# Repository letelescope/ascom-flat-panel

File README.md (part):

# Le Telescope Flat Panel 

[![Build with PlatformIO](https://img.shields.io/badge/build%20with-PlatformIO-orange?logo=data%3Aimage%2Fsvg%2Bxml%3Bbase64%2CPHN2ZyB3aWR0aD0iMjUwMCIgaGVpZ2h0PSIyNTAwIiB2aWV3Qm94PSIwIDAgMjU2IDI1NiIgeG1sbnM9Imh0dHA6Ly93d3cudzMub3JnLzIwMDAvc3ZnIiBwcmVzZXJ2ZUFzcGVjdFJhdGlvPSJ4TWlkWU1pZCI+PHBhdGggZD0iTTEyOCAwQzkzLjgxIDAgNjEuNjY2IDEzLjMxNCAzNy40OSAzNy40OSAxMy4zMTQgNjEuNjY2IDAgOTMuODEgMCAxMjhjMCAzNC4xOSAxMy4zMTQgNjYuMzM0IDM3LjQ5IDkwLjUxQzYxLjY2NiAyNDIuNjg2IDkzLjgxIDI1NiAxMjggMjU2YzM0LjE5IDAgNjYuMzM0LTEzLjMxNCA5MC41MS0zNy40OUMyNDIuNjg2IDE5NC4zMzQgMjU2IDE2Mi4xOSAyNTYgMTI4YzAtMzQuMTktMTMuMzE0LTY2LjMzNC0zNy40OS05MC41MUMxOTQuMzM0IDEzLjMxNCAxNjIuMTkgMCAxMjggMCIgZmlsbD0iI0ZGN0YwMCIvPjxwYXRoIGQ9Ik0yNDkuMzg2IDEyOGMwIDY3LjA0LTU0LjM0NyAxMjEuMzg2LTEyMS4zODYgMTIxLjM4NkM2MC45NiAyNDkuMzg2IDYuNjEzIDE5NS4wNCA2LjYxMyAxMjggNi42MTMgNjAuOTYgNjAuOTYgNi42MTQgMTI4IDYuNjE0YzY3LjA0IDAgMTIxLjM4NiA1NC4zNDYgMTIxLjM4NiAxMjEuMzg2IiBmaWxsPSIjRkZGIi8+PHBhdGggZD0iTTE2MC44NjkgNzQuMDYybDUuMTQ1LTE4LjUzN2M1LjI2NC0uNDcgOS4zOTItNC44ODYgOS4zOTItMTAuMjczIDAtNS43LTQuNjItMTAuMzItMTAuMzItMTAuMzJzLTEwLjMyIDQuNjItMTAuMzIgMTAuMzJjMCAzLjc1NSAyLjAxMyA3LjAzIDUuMDEgOC44MzdsLTUuMDUgMTguMTk1Yy0xNC40MzctMy42Ny0yNi42MjUtMy4zOS0yNi42MjUtMy4zOWwtMi4yNTggMS4wMXYxNDAuODcybDIuMjU4Ljc1M2MxMy42MTQgMCA3My4xNzctNDEuMTMzIDczLjMyMy04NS4yNyAwLTMxLjYyNC0yMS4wMjMtNDUuODI1LTQwLjU1NS01Mi4xOTd6TTE0Ni41MyAxNjQuOGMtMTEuNjE3LTE4LjU1Ny02LjcwNi02MS43NTEgMjMuNjQzLTY3LjkyNSA4LjMyLTEuMzMzIDE4LjUwOSA0LjEzNCAyMS41MSAxNi4yNzkgNy41ODIgMjUuNzY2LTM3LjAxNSA2MS44NDUtNDUuMTUzIDUxLjY0NnptMTguMjE2LTM5Ljc1MmE5LjM5OSA5LjM5OSAwIDAgMC05LjM5OSA5LjM5OSA5LjM5OSA5LjM5OSAwIDAgMCA5LjQgOS4zOTkgOS4zOTkgOS4zOTkgMCAwIDAgOS4zOTgtOS40IDkuMzk5IDkuMzk5IDAgMCAwLTkuMzk5LTkuMzk4em0yLjgxIDguNjcyYTIuMzc0IDIuMzc0IDAgMSAxIDAtNC43NDkgMi4zNzQgMi4zNzQgMCAwIDEgMCA0Ljc0OXoiIGZpbGw9IiNFNTcyMDAiLz48cGF0aCBkPSJNMTAxLjM3MSA3Mi43MDlsLTUuMDIzLTE4LjkwMWMyLjg3NC0xLjgzMiA0Ljc4Ni01LjA0IDQuNzg2LTguNzAxIDAtNS43LTQuNjItMTAuMzItMTAuMzItMTAuMzItNS42OTkgMC0xMC4zMTkgNC42Mi0xMC4zMTkgMTAuMzIgMCA1LjY4MiA0LjU5MiAxMC4yODkgMTAuMjY3IDEwLjMxN0w5NS44IDc0LjM3OGMtMTkuNjA5IDYuNTEtNDAuODg1IDIwLjc0Mi00MC44ODUgNTEuODguNDM2IDQ1LjAxIDU5LjU3MiA4NS4yNjcgNzMuMTg2IDg1LjI2N1Y2OC44OTJzLTEyLjI1Mi0uMDYyLTI2LjcyOSAzLjgxN3ptMTAuMzk1IDkyLjA5Yy04LjEzOCAxMC4yLTUyLjczNS0yNS44OC00NS4xNTQtNTEuNjQ1IDMuMDAyLTEyLjE0NSAxMy4xOS0xNy42MTIgMjEuNTExLTE2LjI4IDMwLjM1IDYuMTc1IDM1LjI2IDQ5LjM2OSAyMy42NDMgNjcuOTI2em0tMTguODItMzkuNDZhOS4zOTkgOS4zOTkgMCAwIDAtOS4zOTkgOS4zOTggOS4zOTkgOS4zOTkgMCAwIDAgOS40IDkuNCA5LjM5OSA5LjM5OSAwIDAgMCA5LjM5OC05LjQgOS4zOTkgOS4zOTkgMCAwIDAtOS4zOTktOS4zOTl6bS0yLjgxIDguNjcxYTIuMzc0IDIuMzc0IDAgMSAxIDAtNC43NDggMi4zNzQgMi4zNzQgMCAwIDEgMCA0Ljc0OHoiIGZpbGw9IiNGRjdGMDAiLz48L3N2Zz4=)](https://platformio.org/)

Open source *ASCOM* and *INDI* driven automated flat panel for astrophotography. 

> ⚠ **DISCLAIMER**  
> This project is still very much work in progress. None of it is likely/expected to work at this stage !

---

## Introduction

This project is an open source initiative, under the MIT license, by *Le Telescope*. This is the v2 of a fully automated and drivable motorized flat panel/dust cap. The device is nicknamed FFFP. Don't ask why! If you still want to know, see the  [misc. section](#miscellaneous) of this readme.

This project should contain all you need to build your own *ASCOM* and/or *INDI* driven Flat Panel. 

- [firmware](./firmware/fffp_firmware/): Firware of the programble chip used to control the panel and its cover
- [drivers](./drivers/): Implementation of the drivers
  - [ASCOM](./drivers/ASCOM/) : Implementation of the *ASCOM* driver 
  - [INDI](./drivers/indi/) : Implementation of the *INDI* driver
- [electronics](./electronics/): Electronic schematics and PCB layouts
- [models](./models/): 3D models for the plat cap
- [specifications](./specifications/): Specifications of the project. Mainly the specs of the communication protocol between the drivers and the firmware.

This project, the protocol, the implementation of both the *ASCOM* driver and the firmware, the electronics and the 3D models are heavily inspired by the the work  of [Dark Sky Geek](https://github.com/jlecomte/). And more precisely: 
- [ascom-flat-panel](https://github.com/jlecomte/ascom-flat-panel)
- [ascom-wireless-flat-panel](https://github.com/jlecomte/ascom-wireless-flat-panel)
- [ascom-telescope-cover-v2](https://github.com/jlecomte/ascom-telescope-cover-v2)

Kudos to him. 

The Pulse Width Modulation (PWM), used to control the panel brightness, implementation is heavily inspired, or more accurately shamelessly ripped, from the work of [Khoih Hoang](https://github.com/khoih-prog) and more precisely [SAMD_PWM](https://github.com/khoih-prog/SAMD_PWM/). 

Kudos to him too.

Finally te INDI driver architecture follows very closely the official [Gemini Flat Panel](https://github.com/indilib/indi/blob/master/drivers/auxiliary/gemini_flatpanel.h) as well as teh [Flip Flat](https://github.com/indilib/indi/blob/master/drivers/auxiliary/flip_flat.h) implemtentations. 

----

## Construction

### Why a "motorized flat panel" ? And what do we mean by "motorized flat panel" ?

In this scenario a flat panel is made of two things
- A light panel with variable brightness
- A motorized cover

The cover is motorized using a servo motor and held in open/close positions using simple magnets. The lightpanel is made 
- either using LEDs and the variable brightness is achieved via pulse width modulation (PWM). 
- or eusing a EL panel and the variable brightness is achived usi a DAC (Digital to Analog Converter) coupled to an OA (Operation Amplifier) in non-inverting amplifier mode. 

This "electronico-mechanical" assembly is controlled via a SAMD21 based board with a custom firmware within a custom PCB. The SAMD21 is particullarly suited because:

- it can output 5V, that is needed to power the servo.
- it can output +3V3 and allow us to choose between 3V and 5V to power the LEDs.
- it has 16 bits timer counters necessary to achieve fast PWM. We do not want flickering flats...
- it has a real DAC output pin to alow "easy" dimming of a flat panel.

One can connect and send commands to the flat-panel using Serial (COM Port) over USB. When plugged in the device will be recognized by windows/linux as a COM device. 

Finally this is driven by ASCOM/INDI, such that one can fully automate taking flats following the acquisition sessions of our beloved night sky targets. 

> ⚠ **DISCLAIMER**  
> This project is built around the Seeeduino XIAO board that uses the ATSAMD21G18A-MU chip. This is the only board that we tested. This may work on other boards that uses these SAMD21 chips, but this may need some rework on the firware, the PCB layout and the mechanical assembly. 

Now that we have the big picture let's get real and build the thing !

[INSERT HERE SOME PHOTOS]

### Pre-requisites

Very few pre-requisites are necessary in order to build the flat panel. More precisely one will need to:

- have access to a 3D printer, to print the mechanical assembly parts
- have some soldering skills and a soldering kit, to solder the components to the custom PCB
- install PlateformIO, to upload the firmware
- love "diy-ing", because you may need to want/need to tweaks things a bit to make it work in your setup. 
  
And that's it ! For instance you won't need software developpement skills as both the driver and the firmware are usable as is. Moreover, the ASCOM driver installer is already pre-compiled and made available to the download. Unfortunaltely one cannot make an "installer" for the arduino firware. Yet using PlaterfomIO to upload the firmware is a matter of three clicks. 

> We chose PlatformIO instead of ArduinoIDE due to recent concerns about Arduino's Open Source commitment under Qualcomm, and ,icing on the cake, PlatformIO provides superior dependency and library management.

### Bill of material 

[TODO] ADD BILL OF MATERIAL 

### Get a coherent version. 

We heavily use the git version control "tags" to label released versions. We also leverage the "GitHub releases" that add the possibility to pin "binaries" (ie anything we want PCB layouts, Driver installers, mechanincal assembly 3D printer files,...) on "tagged" versions. 

When we deem a version is "usable" we tag it, ie we freeze this repository at a particular "commit", and create a release out of it. 

To access the various releases just got the [releases page](https://github.com/letelescope/ascom-flat-panel/releases/) of this repository.

And choose the release you want. The latest should be the "better". 

We recommend that you use one of these released version as they are coherent and tested. Be careful some release are labelled "pre-release" and should be used with caution. Those are developpement, beta and alpha version. Use it at you own risk like all the material on this repository. But even more in this case :D. 

In the same spirit, we do not recommend you use the "head" of the main branch (or any other branch) of this repository as this is work in progress and hence is not guaranteed to be stable or even usable...

> If you already have an FFFPV1, please note that both drivers and firmware **should** be backward compatible. You can use the latest version of both the ASCOM driver with your FFFPV1 without any issue and vice-versa: upload the new firmware on your FFFPV1 device and still use the legacy v1 driver. Yet we recommend you use the latest version of the driver, the firmware, the electronic circuit and the assembly as they all have been improved coherently.

### Electronic circuit

We provide three options for the electronic circuit. The difference is made on wether you want to use a led panel or a EL panel (You may not have the choice, as LED panels are restricted to smaller diameters). 

#### EL Panel option

This is certainely the "go to" solution, as this allows for a slicker and ligther mechanical assembly. Ans the electronics are not that much more difficut. 

- The The Pin "AO" (DAC) of the Seeeduino XIAO is used to control the LED brightness:
  - Is is directly connected to the non-invervint pin of ta TLC272 Op.Amp. The Ration of R1/R2 controls the amplifying contant (R = 1 + R1/R2) 
  - The output of the TLC272 is connected to the base of a  darlington transistor. Such that more current can flow to the EL Driver without worring too much about the life expectency of the TLC272
  -  The +12v needed for the Op Amp and the Driver is obtained using a DC/DC regulator

> ⚠ **WARNING**  
> The choice of Pin AO for DAC is not random. This is the only one on the Seeeduino XIAO (and SAM-D21 chips) capable to produce proper DAC. Please [see](https://ww1.microchip.com/downloads/en/DeviceDoc/SAM_D21_DA1_Family_DataSheet_DS40001882F.pdf). 

- The Pins "5,6,7"  of the Seeeduino XIAO are used for power control, position control and servo feedback:
  - Power control is connected, via a voltage divider bridge, to the gate of a IRLZ34N MOSFET.
  - Feedback is directly connected to the feedback pin of the servo.
  - Position control is directly connected to the position control pin of the servo.
  
- Servo VCC and Servo ground are decoupled using diodes.

- +12V and +5V are decoupled from ground using 10μF capacitors. It acts both as
  - an energy storage for a stable +5V/+12V output.
  - a "wire" for very high frequency spurious oscillations and effectively ground them. 

#### LED Panel schematics

This should be the go solution for most setups. Yet if you setup si particularly slow you may want to check the led versions. 

Here is the schematics for this option

#### LED panel option

There are two options regarding the tension value used to power the LEDs: either +3V3 or +5V. But appart from that the two circuits share the same principles:

- The Pin "8"  of the Seeeduino XIAO is used to control the LED brightness:
  + It is connected, via a voltage divider bridge, to the gate of a IRLZ34N MOSFET.
  - The "+"terminal of the LEDs (strip or panel) is plugged to the constant +3V3 (or +5V) output of the Seeeduino
  - The "-" terminal of the LEDs (strip or panel) is connected to the drain of the IRLZ34N MOSFET. 
  - The source of the MOSFET is grounded. 
  - High frenquency PWM is used to swich rapidly ON and OFF the MOSFET, and allow to control the effective tension applied to the LEDs. 

> ⚠ **WARNING**  
> The choice of Pin 8 for PWM is not random. Not all pins of Seeeduino XIAO (and SAM-D21 chips) are capable to produce high frequency PWM. That's possible with Pin 8 because it use timer counter TCC1 which is 16bits.  And If you want to choose another pin please check the [documentation](https://ww1.microchip.com/downloads/en/DeviceDoc/SAM_D21_DA1_Family_DataSheet_DS40001882F.pdf) first. 

- The Pins "5,6,7"  of the Seeeduino XIAO are used for power control, position control and servo feedback:
  - Power control is connected, via a voltage divider bridge, to the gate of a IRLZ34N MOSFET.
  - Feedback is directly connected to the feedback pin of the servo.
  - Position control is directly connected to the position control pin of the servo.
  
- Servo VCC and Servo ground are decoupled using diodes.

- +5V (and +3V3 if needed) are decoupled from ground using 10μF capacitors. It acts both as
  - an energy storage for a stable +5V/+3V3 output.
  - a "wire" for very high frequency spurious oscillations and effectively ground them. 

##### The +3V3 output for LEDs

This is best suited for small refractors using fewer LEDs and/or fast optics. 

Here is the schematics for this option

##### The +5V output for LEDs

This is best suited for bigger tubes using a larger number of LEDs drawing more current. 

#### Cicruit layout breadbord validation

We recommend you prototype the circuit using breadbords first. 

- This can help you choose between the +5V and +3V3 version. A quick "hint", don't go for to bright ouputs for LEDs as a very bright panel is in fact not really needed when taking flats. Especially with fast optics. 
- This allows to check each component/part of the circuit independently. It's always better to find a faulty component before it is soldered on a PCB.
- It's always fun to prototype. 

Here is and example of what the "+5V" circuit may look like on a breadbord.

.

#### Printed Circuit Board

We had our PCBs printed by [PCBWay](https://www.pcbway.com/). If you do not modify the PCB layout and want to have it printed by PCBWay, you can just download one of the provided zip files that are pinned to the release (fffpv1-electronics-5V-LEDs-pcbway-files.zip or fffpv1-electronics-3V-LEDs-pcbway-files.zip, depending if you intend to use the +5V or +3V3 version).

If you want to modify the PCB layout, you have two options depending on the company you chose to print your PCB :
- If you chose PCBWay, just run a "Desing Rules Check" after your modifications are done to make sure there is no error (there may be warnings, but who cares about warnings ?). The PCBWay design rules are associated to the KiCAD project (they are implemented in the ascom-flat-panel.kicad_dru file). From here you can generate the fabrication files using the KiCAD interface and following the recommandations explained on the PCBWay website, OR you can simply install the PCBWay plugin for KiCAD, which will do the job for you in one click, and will drive you to the PCBWay website to complete your order (yes, we live in a fantastic era).
- If you chose another company, make sure their design rules are implemented to the KiCAD project. Depending on the company, you may find them in tables on the company's website and implement them using the KiCAD interface, or they can provide a .kicad_dru file you can use instead of the one we provide. Then perform a "Desing Rules Check" to check your modifications. Then you can generate the fabrication files using the KiCAD interface and following the recommandations provided by your supplier, or you can find out if there is a KiCAD plugin to do the job. Some suppliers will just take your KiCAD project and do all of this by their own, leaving you with basically nothing to do but creating an account and uploading your project (and pay, of course).

#### Firmware upload

#### Pre-requisite

The firmware needs to be uploaded using Visual Studio Code/PlateformIO . [PlateformIO setup section](#pre-requisites-1) of this documentation to set it. 

#### Upload the firware

1. Open the [firmware project](./firmware/fffp) from Visula Strudio Code/Plateform-IO. 

2. Connect the board via US. 
   
3. Select the board.
   
4. Click the "arrow" at the bottom to compile and upload the firmware on the board. 

The output should look something like: 

#### Firmware checks

Once the firware is uploaded, do not disconnect the board yet. Still from the Arduino IDE open the "Serial Monitor". Once connected, in the console type:

``` console
COMMAND:PING
```
the board should answer

``` console
RESULT:PONG
```

Congrats! The Seeeduino is ready to act as your flat panel controller !

### Mechanical Assembly

Moving on to the actual print and build of the assembly. 

#### Prints from pre-designed assemblies

This repository (and therefore the tagged release version) contains a fully fonctional model. This is made to fit an Askar SQA-55 and uses premade 100mm led panel. It also feature an adapter to fit an Askar 71F. 

"Ready to print" STL files are also pinned to the release. Just download the fffpv1-100mm_led_pan_diam_stl.zip archive, unzip it. The archiver files are organized within two folders "Black" and "White". Files in he "black" repository can be printed in the color of your choice, but the one in the "white" folder should be printed using white PLA for better performance. This is especially true for the "spacer/diffuser" that, as its name suggests, helps homogenise the illumination of the panel.

#### Modification of pre-designed assemblies

#### Manufacturing sequence

#### Calibration of servo motor 

> ⚠ **WARNING**
> The firmware needs to be calibrated.

At first boot the LEDs will flash to indicate that it needs to be calibrated. 

> ⚠ **WARNING**
> Disconnect the servo from the mecanical assembly before launching the calibration procedure. 

Then from the IDE connect to the board and using the Arduino serial monitor send (type) the "command" 

``` console
COMMAND:COVER_CALIBRATION_RUN
``` 

The device should perform its calibration procedure and reply with 

``` console
RESULT:COVER_CALIBRATION_RUN@OK
```

Once it has completed, re-attach the right arm to the servo. The device is now ready to be used.

### ASCOM Driver Install

You can either used the installer to install the ASCOM driver or build it from source. For the sake of simplicity we recommend using the installer. 

#### Pre-compiled installer

The installer is pined on each release [releases page](https://github.com/letelescope/ascom-flat-panel/releases/). 

1. From the wanted release, download the file "FFFP_Setup.exe". 

2. "Double-click" on the downloaded file to launch it. 

   > ⚠ **WARNING**
   > Windows will warn that the publisher is unknown. This is perfectly fine. As buying a verified signing key, is definitely not a priority for us, we could not sign the installer. Yet this is perfectly safe to use it. 

3. Follow the instruction to install and register the driver. 

Congrats! You just installed the driver !

#### Build from sources

To build it from source please check the relevant section of the "developpement documentation". 

#### Driver validation

Once install is complete, one can use the ASCOM profile explorer tool to check that this was installed properly. From the ASCOM profile explorer check that the *ASCOM CoverCalibrator Drvier for Le Telescope FFFP* is listed in the Cover Calibrators. 

### INDI Driver

> ⚠ **WARNING**
> INDO driver is NOT functional DO NOT USE IT. 

---

## Testing

To avoid mass troubleshooting, one can test each component fairly separately. Below are listed some tests that can be used to validate the setup. Going from "unit test" to big-bang integration tests from your favourite acquisition software. 

### Firware "unit" testing

Once the firware is uploaded, one should already have tested that the seeduino was responsive. If not, reconnect the board via USB. From the Arduino IDE, open the "Serial Monitor". Once connected, in the console type:

``` console
COMMAND:PING
```
the board should answer

``` console
RESULT:PONG
```
If that's not the case, please make sure that you uploaded the (correct version of the) firmware firt. 

If that is indeed the case, congrats you are ready to test more "interesting" features of the firmware.

#### Set brightness levels

From the "Serial Monitor", in the console type the following command to adjust the LED panel brightness level:

``` console
COMMAND:BRIGHTNESS_SET@1024
```
the board should answer in the console

``` console
RESULT:BRIGHTNESS_SET@1024
```
In parallel, if it is connected to the board, the light panel should have been turned on. Feel free to change the value (number after the '@') to adjust the brightness. Max allowed value is 2047 and min value is 0. 

Use ```COMMAND:BRIGHTNESS_RESET``` to switch off the panel.

Congrats the variable light panel is functionnal. 

#### Open/Close the cover

> ⚠ **WARNING**
> To be able to open/close the panel, the panel should be calibrated first. Check the "mechanical assembly" section for the procedure. 

When turned on, the panel should be closed. To open it, from the "Serial Monitor", in the console type the following command:

``` console
COMMAND:COVER_OPEN
```
the panel should start moving and the board should answer in the console

``` console
RESULT:COVER_OPEN@OK
```

Once open to close it simply type in the consle

``` console
COMMAND:COVER_CLOSE
```
the panel should start moving and the board should answer in the console

``` console
RESULT:COVER_CLOSE@OK
```

Finally at any given time, to know the status of the mecanical panel type 

``` console
COMMAND:COVER_GET_STATE
```
the panel should start moving and the board should answer in the console

``` console
RESULT:COVER_GET@{panel.cover}
```

where panel.cover is string human readable translation of the current cover state. Possible values are in [**OPEN**, **OPENING**, **CLOSING**,]; 

Congrats the motorized cover is functionnal. 

### Driver "unit testing"

After install completion, one should already have used the ASCOM profile explorer tool to check that this was installed properly. If that's not the case from the ASCOM profile explorer check that the *ASCOM CoverCalibrator Drvier for Le Telescope FFFP* is listed in the Cover Calibrators. 

1. Then check that the driver is instiable using the ASCOM diagnostic tools
   
   a. Select the "Cover Calibrator" device type and elect the "FFPV1 Cover Calibrator"

   b. Find and configure the "properties" of the driver

   b. Connect to the driver. Expect nothing much to happen. 

Congrats the driver seems to work as expected !

### Connect to the panel from N.I.N.A via ASCOM

Great ! If you read this, at this stage, the firware, the driver and the mecanical assembly should work, or at least one should be confident enough that they are working. Let's make the final test (and the only one relevant in fact). Let's take some flats from N.I.N.A. 

## Usage

The FFFP should be now be fully usable and drivable from N.I.N.A. 

### Flat-Panel Connection

Let's connect to the flat panel. 

0. Plug the flat panel to the computer via USB

In the equipment tab, from the flat panel section:

1. Select the *ASCOM CoverCalibrator Drvier for Le Telescope FFFP*.
2. Click the gear icon and select the correct COM Port. 
3. Hit OK to save the configuration.

4. Click the "power" button to connect to the flat panel. 

From there you can turn on and off the panel, set the wanted brightness and/or open/close the cover. 

### N.I.N.A smart flats

Let's now use the N.I.N.A smart flats capabilities to automate flat frames recording.

#### Auto-exposure

#### Auto-brightness

---

## Developpement 

### Principle

In this scenario a flat panel is made of two things
- A light panel with variable brightness
- A motorized cover

The firmware updates the state of the flat panel upon instructions of the (*ASCOM* or *INDI*) driver. The communication protocol is serial based. The serial connection is established via USB. Here is a a summary of the protocol 
- Both the driver and the flat panel (its firmware) exchange single line messages; ie terminated by '\n'.
- A message is structured as TYPE:MESSAGE, where TYPE is in "COMMAND, RESULT, ERROR" and MESSAGE is alaphanumerical with spaces and "@"

The driver emmits and the firmware handles the incoming "COMMAND" messages. This kind of message is stuctured as 

- `COMMAND:NAME[@ARGS]` where NAME is [A-Z_]+ and ARGS may be optional or mandatory and their nature may depend on the command.

The firmware then responds with 
- either a `RESULT:CMD_NAME@VALUE` if operation succeeded
- or an `ERROR:ERR_MESSAGE@DETAILS` if anything went wrong

In a nutshell

     -----------------                           ------------
    |                 |                         |            |
    |      Driver     | COMMAND:CMD_NAME[@ARGS] | Flat Panel |
    | (ASCOM or INDI) | --------------------->  | (firmware) |
    |                 | <---------------------  |            |
     -----------------  RESULT:CMD_NAME@VALUE    ------------
                                or
                        ERROR:ERR_MESSAGE@DETAILS

More details on this protocol are provided in [protocol.md](./specifications/protocol.md)

### Softwares developpement and compilations

#### Seeduino firmware

The firware is entirely buildable and uploadable using the Arduino IDE
 
##### Pre-requisites 

- [Download](https://code.visualstudio.com/download) and install the Visual Studio Code or the IDE of your choice
- [Download](https://platformio.org/install/ide) PlatformIO IDE and/or install the PlatformIO extension for Visual Studio Code
- No need to download and configure the Seeduino XIAO board for PlateformIO as this is already done in the [platformio.ini](./firmware/fffp_firmware/platformio.ini) file of the firmware project.
- No need to download and install the official Adafruit SleepyDog library  as this is already done in the [platformio.ini](./firmware/fffp_firmware/platformio.ini). This is used to properly handle disconnection. 

##### Compile and upload the firmware

1) Using PlateformIO IDE, open the [project](./firmware/fffp_firmware/)

2) Click "PlateformIO: Build" to compile the firmware. The output should be something like 
   ``` console
   Processing seeed_xiao (platform: atmelsam; board: seeed_xiao; framework: arduino)
   --------------------------------------------------------------------------------------------------------------------------------------------------
   Verbose mode can be enabled via `-v, --verbose` option
   CONFIGURATION: https://docs.platformio.org/page/boards/atmelsam/seeed_xiao.html
   PLATFORM: Atmel SAM (8.3.0) > Seeeduino XIAO
   HARDWARE: SAMD21G18A 48MHz, 32KB RAM, 256KB Flash
   DEBUG: Current (atmel-ice) External (atmel-ice, blackmagic, jlink)
   PACKAGES:
    - framework-arduino-samd-seeed @ 1.8.5
    - framework-cmsis @ 2.50400.181126 (5.4.0)
    - framework-cmsis-atmel @ 1.2.2
    - toolchain-gccarmnoneeabi @ 1.70201.0 (7.2.1)
   LDF: Library Dependency Finder -> https://bit.ly/configure-pio-ldf
   LDF Modes: Finder ~ chain, Compatibility ~ soft
   Found 20 compatible libraries
   Scanning dependencies...
   Dependency Graph
   |-- Servo @ 1.3.0
   |-- Adafruit SleepyDog Library @ 1.6.5
   |-- FF_Flat_Panel
   |-- FlashStorage @ 0.5.0
   |-- SAMD21_PWM
   Building in release mode
   Compiling .pio\build\seeed_xiao\src\main.cpp.o
   Compiling .pio\build\seeed_xiao\libae5\Servo\avr\Servo.cpp.o
   Compiling .pio\build\seeed_xiao\libae5\Servo\esp32\Servo.cpp.o
   Compiling .pio\build\seeed_xiao\libae5\Servo\mbed\Servo.cpp.o
   Compiling .pio\build\seeed_xiao\libae5\Servo\megaavr\Servo.cpp.o
   Compiling .pio\build\seeed_xiao\libae5\Servo\nrf52\Servo.cpp.o
   Compiling .pio\build\seeed_xiao\libae5\Servo\renesas\Servo.cpp.o
   Compiling .pio\build\seeed_xiao\libae5\Servo\sam\Servo.cpp.o
   Compiling .pio\build\seeed_xiao\libae5\Servo\samd\Servo.cpp.o
   Compiling .pio\build\seeed_xiao\libae5\Servo\stm32f4\Servo.cpp.o
   Compiling .pio\build\seeed_xiao\libae5\Servo\xmc\Servo.cpp.o
   Compiling .pio\build\seeed_xiao\libae5\Servo\zephyr\Servo.cpp.o
   Compiling .pio\build\seeed_xiao\lib2bf\Adafruit SleepyDog Library\Adafruit_SleepyDog.cpp.o
   Compiling .pio\build\seeed_xiao\lib2bf\Adafruit SleepyDog Library\utility\WatchdogAVR.cpp.o
   Compiling .pio\build\seeed_xiao\lib2bf\Adafruit SleepyDog Library\utility\WatchdogESP32.cpp.o
   Compiling .pio\build\seeed_xiao\lib2bf\Adafruit SleepyDog Library\utility\WatchdogESP8266.cpp.o
   Compiling .pio\build\seeed_xiao\lib2bf\Adafruit SleepyDog Library\utility\WatchdogKinetisK.cpp.o
   Compiling .pio\build\seeed_xiao\lib2bf\Adafruit SleepyDog Library\utility\WatchdogKinetisL.cpp.o
   Compiling .pio\build\seeed_xiao\lib2bf\Adafruit SleepyDog Library\utility\WatchdogNRF.cpp.o
   Compiling .pio\build\seeed_xiao\lib2bf\Adafruit SleepyDog Library\utility\WatchdogRP2040.cpp.o
   Compiling .pio\build\seeed_xiao\lib2bf\Adafruit SleepyDog Library\utility\WatchdogSAMD.cpp.o
   Compiling .pio\build\seeed_xiao\libc78\FlashStorage\FlashStorage.cpp.o
   Archiving .pio\build\seeed_xiao\libae5\libServo.a
   Compiling .pio\build\seeed_xiao\FrameworkArduinoVariant\variant.cpp.o
   Compiling .pio\build\seeed_xiao\FrameworkArduino\IPAddress.cpp.o
   Compiling .pio\build\seeed_xiao\FrameworkArduino\IPv6Address.cpp.o
   Archiving .pio\build\seeed_xiao\lib2bf\libAdafruit SleepyDog Library.a
   Compiling .pio\build\seeed_xiao\FrameworkArduino\Print.cpp.o
   Compiling .pio\build\seeed_xiao\FrameworkArduino\Reset.cpp.o
   Compiling .pio\build\seeed_xiao\FrameworkArduino\Retarget.cpp.o
   Compiling .pio\build\seeed_xiao\FrameworkArduino\SERCOM.cpp.o
   Archiving .pio\build\seeed_xiao\libc78\libFlashStorage.a
   Archiving .pio\build\seeed_xiao\libFrameworkArduinoVariant.a
   Compiling .pio\build\seeed_xiao\FrameworkArduino\Stream.cpp.o
   Compiling .pio\build\seeed_xiao\FrameworkArduino\StreamString.cpp.o
   Compiling .pio\build\seeed_xiao\FrameworkArduino\Tone.cpp.o
   Compiling .pio\build\seeed_xiao\FrameworkArduino\USB\CDC.cpp.o
   Compiling .pio\build\seeed_xiao\FrameworkArduino\USB\PluggableUSB.cpp.o
   Compiling .pio\build\seeed_xiao\FrameworkArduino\USB\SAMD21_USBDevice.cpp.o
   Compiling .pio\build\seeed_xiao\FrameworkArduino\USB\USBCore.cpp.o
   Compiling .pio\build\seeed_xiao\FrameworkArduino\USB\samd21_host.c.o
   Compiling .pio\build\seeed_xiao\FrameworkArduino\Uart.cpp.o
   Compiling .pio\build\seeed_xiao\FrameworkArduino\WInterrupts.c.o
   Compiling .pio\build\seeed_xiao\FrameworkArduino\WMath.cpp.o
   Compiling .pio\build\seeed_xiao\FrameworkArduino\WString.cpp.o
   Compiling .pio\build\seeed_xiao\FrameworkArduino\abi.cpp.o
   Compiling .pio\build\seeed_xiao\FrameworkArduino\avr\dtostrf.c.o
   Compiling .pio\build\seeed_xiao\FrameworkArduino\base64.cpp.o
   Compiling .pio\build\seeed_xiao\FrameworkArduino\cbuf.cpp.o
   Compiling .pio\build\seeed_xiao\FrameworkArduino\cortex_handlers.c.o
   Compiling .pio\build\seeed_xiao\FrameworkArduino\delay.c.o
   Compiling .pio\build\seeed_xiao\FrameworkArduino\hooks.c.o
   Compiling .pio\build\seeed_xiao\FrameworkArduino\itoa.c.o
   Compiling .pio\build\seeed_xiao\FrameworkArduino\libb64\cdecode.c.o
   Compiling .pio\build\seeed_xiao\FrameworkArduino\libb64\cencode.c.o
   Compiling .pio\build\seeed_xiao\FrameworkArduino\main.cpp.o
   Compiling .pio\build\seeed_xiao\FrameworkArduino\math_helper.c.o
   Compiling .pio\build\seeed_xiao\FrameworkArduino\new.cpp.o
   Compiling .pio\build\seeed_xiao\FrameworkArduino\pulse.c.o
   Compiling .pio\build\seeed_xiao\FrameworkArduino\pulse_asm.S.o
   Compiling .pio\build\seeed_xiao\FrameworkArduino\startup.c.o
   Compiling .pio\build\seeed_xiao\FrameworkArduino\wiring.c.o
   Compiling .pio\build\seeed_xiao\FrameworkArduino\wiring_analog.c.o
   Compiling .pio\build\seeed_xiao\FrameworkArduino\wiring_digital.c.o
   Compiling .pio\build\seeed_xiao\FrameworkArduino\wiring_private.c.o
   Compiling .pio\build\seeed_xiao\FrameworkArduino\wiring_pwm.cpp.o
   Compiling .pio\build\seeed_xiao\FrameworkArduino\wiring_shift.c.o
   C:\Users\fgautier\.platformio\packages\framework-arduino-samd-seeed\cores\arduino\wiring_analog.c:35:12: warning: '_dacResolution' defined but not used [-Wunused-variable]
    static int _dacResolution = 10;
               ^~~~~~~~~~~~~~
   C:\Users\fgautier\.platformio\packages\framework-arduino-samd-seeed\cores\arduino\wiring_pwm.cpp: In function 'void noPwm(uint32_t)':
   C:\Users\fgautier\.platformio\packages\framework-arduino-samd-seeed\cores\arduino\wiring_pwm.cpp:374:13: warning: unused variable 'tcChannel' [-Wunused-variable]
        uint8_t tcChannel = GetTCChannelNumber(pinDesc.ulPWMChannel);
                ^~~~~~~~~
   Archiving .pio\build\seeed_xiao\libFrameworkArduino.a
   Linking .pio\build\seeed_xiao\firmware.elf
   c:/users/fgautier/.platformio/packages/toolchain-gccarmnoneeabi/bin/../lib/gcc/arm-none-eabi/7.2.1/../../../../arm-none-eabi/bin/ld.exe: warning: changing start of section .bss by 4 bytes
   c:/users/fgautier/.platformio/packages/toolchain-gccarmnoneeabi/bin/../lib/gcc/arm-none-eabi/7.2.1/../../../../arm-none-eabi/bin/ld.exe: warning: changing start of section .bss by 4 bytes
   c:/users/fgautier/.platformio/packages/toolchain-gccarmnoneeabi/bin/../lib/gcc/arm-none-eabi/7.2.1/../../../../arm-none-eabi/bin/ld.exe: warning: changing start of section .bss by 4 bytes
   c:/users/fgautier/.platformio/packages/toolchain-gccarmnoneeabi/bin/../lib/gcc/arm-none-eabi/7.2.1/../../../../arm-none-eabi/bin/ld.exe: warning: changing start of section .bss by 4 bytes
   c:/users/fgautier/.platformio/packages/toolchain-gccarmnoneeabi/bin/../lib/gcc/arm-none-eabi/7.2.1/../../../../arm-none-eabi/bin/ld.exe: warning: changing start of section .bss by 4 bytes
   Checking size .pio\build\seeed_xiao\firmware.elf
   Advanced Memory Usage is available via "PlatformIO Home > Project Inspect"
   RAM:   [=         ]   9.4% (used 3064 bytes from 32768 bytes)
   Flash: [==        ]  15.2% (used 39768 bytes from 262144 bytes)
   Building .pio\build\seeed_xiao\firmware.bin
   ========================================================== [SUCCESS] Took 7.97 seconds ==========================================================
   ```

   Don't worry to much about the warnings. Those are only warnings and can be safely igonered c.f. [arduino forum](https://forum.arduino.cc/t/web-ide-error-changing-start-of-section-by-4-bytes/1218049) and [adafruit forum](https://forums.adafruit.com/viewtopic.php?t=189483#p917530) .

1) Connect the Seeeduino and  "PlateformIO: Build"to test it

##### Warning - Firmware calibrarion

The firmware needs to be calibrated. At first boot the leds will flash to indicate that it needs to be calibrated. 

> **WARNING**
> Disconnect the servo from the mecanical assembly before launching the calibration procedure. 

Then from the IDE connect to the board and using the Arduino serial monitor send (type) the "command" 

``` console
COMMAND:COVER_CALIBRATION_RUN
``` 

The device should perform its calibration procedure and reply with 

``` console
RESULT:COVER_CALIBRATION_RUN@OK
```

Once it has completed, re-attach the right arm to the servo. The device is now ready to be used.

#### ASCOM Driver

The ASCOM driver is a C# .Net project that have been first created using the ASCOM 6 Visual Studio 2022 templates. Hence we recommend using Visual Studio 2022 when building it. Feel free to change this procedure to match your tooling. 

##### Pre-requisites 
 
- [ASCOM 7](https://github.com/ASCOMInitiative/ASCOMPlatform/releases/tag/v7.1.1) plateform
- [Visual Studio 2022](https://visualstudio.microsoft.com/fr/vs/). Comunity edition is totally fine. 
- A fully functional [ASCOM developper environement](https://ascom-standards.org/COMDeveloper/Index.htm) . Especiall, you may want to add the ASCOM "extensions" to Visual Studio.

##### Compile and register the driver

1) Open the ["solution"](./drivers/ASCOM/ASCOM_7_Driver/ASCOM_7_Driver.sln) from Visual Studio 2022

2) Compile the project using "Ctrl + Shift + B". The result in the console should look something like
  
   ``` console
   Génération démarrée à 14:12...
   1>------ Début de la génération : Projet : ASCOM_7_Driver, Configuration : Debug Any CPU ------
   1>  ASCOM_6_Driver -> D:\Documents\Perso\Astro\diy\ascom-flat-panel\ASCOM_drivers\ASCOM_7_Driver\bin\Debug\ASCOM.LeTelescopeFFFPV1.exe
   ========== Build : 1 réussite(s), 0 échec(s), 0 à jour, 0 ignorée(s) ==========
   ========== Build s’est terminée à 14:12 et a duré 10,405 secondes ==========
   ```

3) The first time you compile the server you must "register it" on the ASCOM plateform. Open an "elevated" command prompt (with admin priviledges) at the folder where the local server executable is located. Run the local server exe with the /regserver parameter which will create the entry that appears in the ASCOM Chooser. 
  
   ``` console
   .\ASCOM.LeTelescopeFFFP.exe /regserver
   ```

   **This registration only needs to be done once*.

4) You can now launch the driver from any ASCOM client, e.g. N.I.N.A or the ASCOM Diagnostic tool

##### Warning - When used with N.I.N.A

As of N.I.N.A 3.1.HF2, the "ASCOM device instance reference " is not disposed when connection failed. In our setup this may happen if the flat panel is not connected to the PC. In this scenario, the connection will fail, but a "driver process" will hang, waiting for N.I.N.A to dispose of the reference.

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
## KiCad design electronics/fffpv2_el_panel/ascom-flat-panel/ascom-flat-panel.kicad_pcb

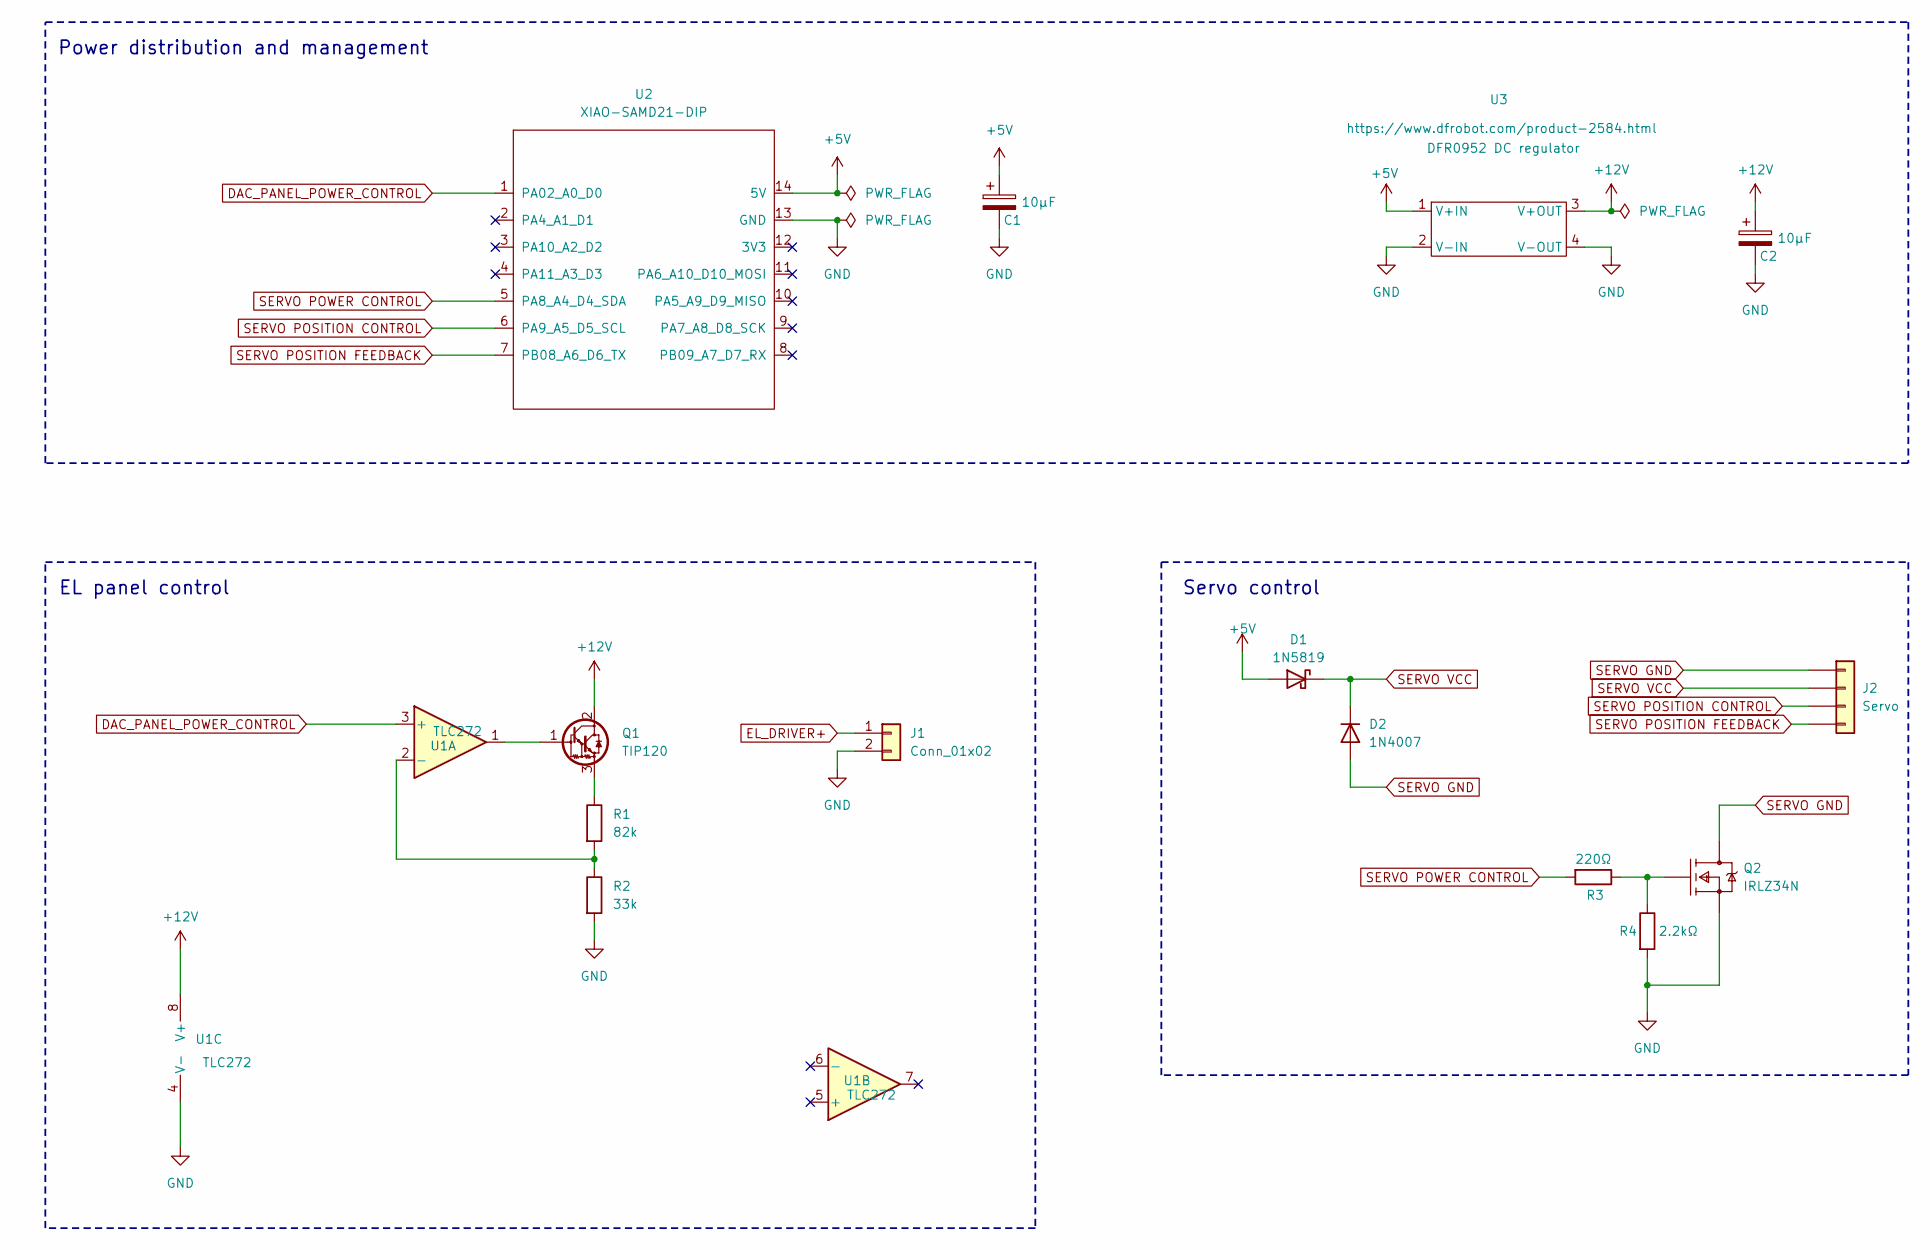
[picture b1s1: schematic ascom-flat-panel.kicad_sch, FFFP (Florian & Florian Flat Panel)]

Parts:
C1, C2: 10µF; C_Radial_D6.3mm_H11.0mm_P2.50mm
D1: 1N5819; D_DO-41_SOD81_P10.16mm_Horizontal
D2: 1N4007; D_DO-41_SOD81_P10.16mm_Horizontal
J1: Conn_01x02; JST_XH_B2B-XH-A_1x02_P2.50mm_Vertical
J2: Servo; PinHeader_1x04_P2.54mm_Vertical
Q1: TIP120; TO-220-3_Vertical
Q2: IRLZ34N; TO-220-3_Vertical; breakdown voltage drain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 60 V; current rating 32 A; mouser part number 512-FQP30N06L; digikey description MOSFET N-CH 60V 32A TO-220
R1: 82k; R_Axial_DIN0207_L6.3mm_D2.5mm_P10.16mm_Horizontal
R2: 33k; R_Axial_DIN0207_L6.3mm_D2.5mm_P10.16mm_Horizontal
R3: 220Ω; R_Axial_DIN0207_L6.3mm_D2.5mm_P10.16mm_Horizontal
R4: 2.2kΩ; R_Axial_DIN0207_L6.3mm_D2.5mm_P10.16mm_Horizontal
U1: TLC272; DIP-8_W7.62mm
U2: XIAO-SAMD21-DIP
U3: DFR052 DC regulator

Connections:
+5V: C1.1, D1.2 (A), U2.14 (5V), U3.1 (V+IN)
+12V: C2.1, Q1.2 (C), U1.8 (V+), U3.3 (V+OUT)
DAC_PANEL_POWER_CONTROL: U1.3 (+), U2.1 (PA02_A0_D0)
EL_DRIVER+: Q1.3 (E), R1.1; also elsewhere on the board
GND: C1.2, C2.2, J1.2, Q2.3 (S), R2.2, R4.2, U1.4 (V-), U2.13 (GND), U3.2 (V-IN), U3.4 (V-OUT); also elsewhere on the board
unnamed: Q1.1 (B), U1.1
unnamed: Q2.1 (G), R3.1, R4.1
unnamed: R1.2, R2.1, U1.2 (-)
SERVO GND: D2.2 (A), J2.1, Q2.2 (D)
SERVO POSITION CONTROL: J2.3, U2.6 (PA9_A5_D5_SCL)
SERVO POSITION FEEDBACK: J2.4, U2.7 (PB08_A6_D6_TX)
SERVO POWER CONTROL: R3.2, U2.5 (PA8_A4_D4_SDA)
SERVO VCC: D1.1 (K), D2.1 (K), J2.2

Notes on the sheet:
Servo control
Power distribution and management
EL panel control

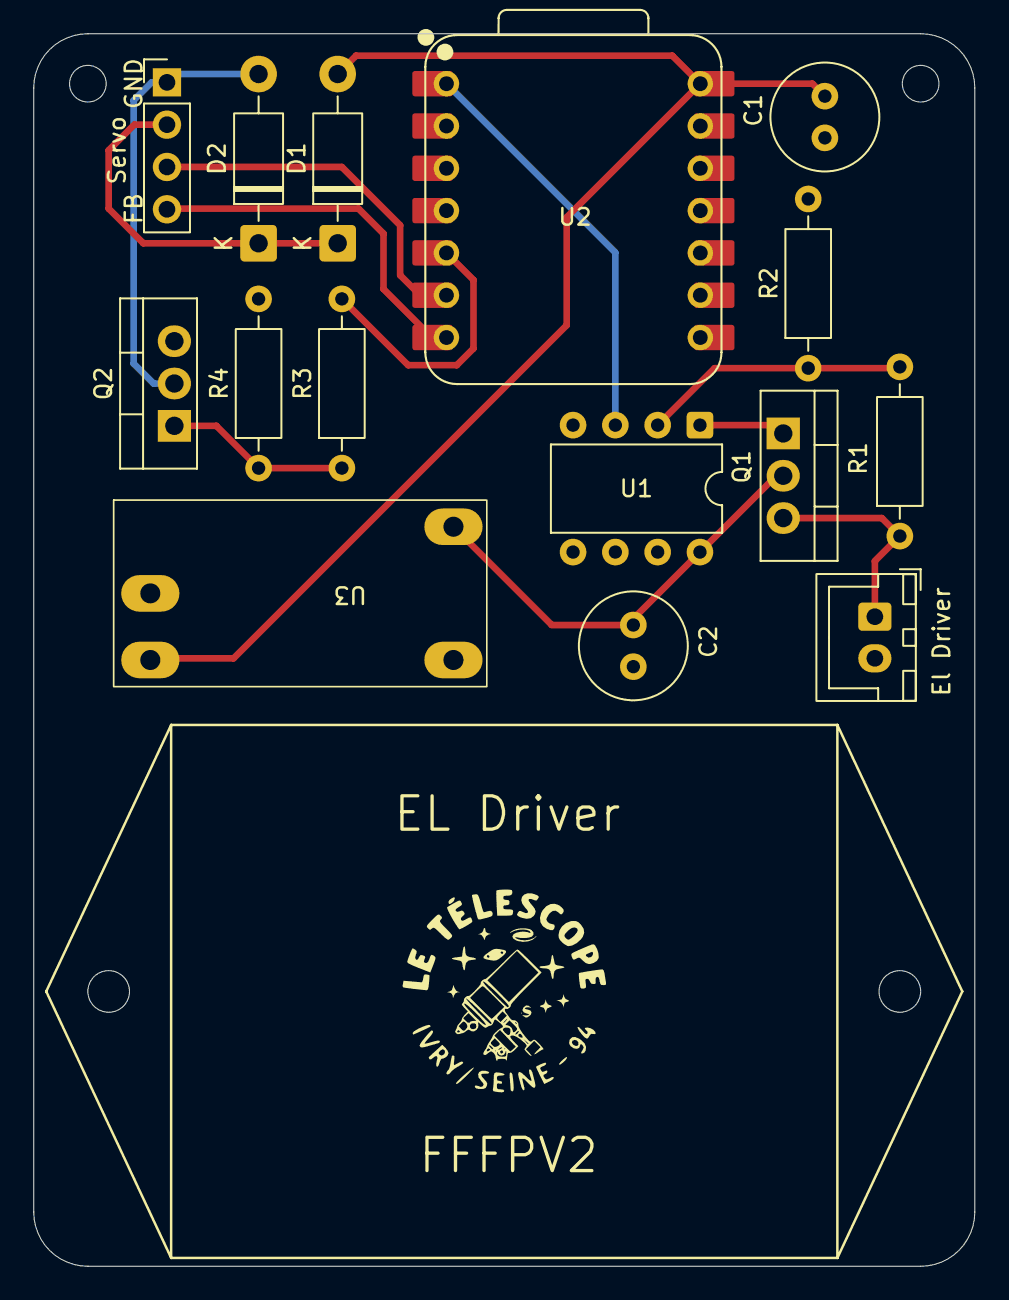
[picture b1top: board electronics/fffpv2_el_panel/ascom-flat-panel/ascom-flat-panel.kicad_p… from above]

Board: 2 copper layers, 56.5 x 74.0 mm, 15 parts (0 on the bottom side), 13 nets.

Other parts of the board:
El Driver: Conn_01x02; JST_XH_B2B-XH-A_1x02_P2.50mm_Vertical

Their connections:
EL_DRIVER+: El Driver.1; also elsewhere on the board
GND: El Driver.2; also elsewhere on the board

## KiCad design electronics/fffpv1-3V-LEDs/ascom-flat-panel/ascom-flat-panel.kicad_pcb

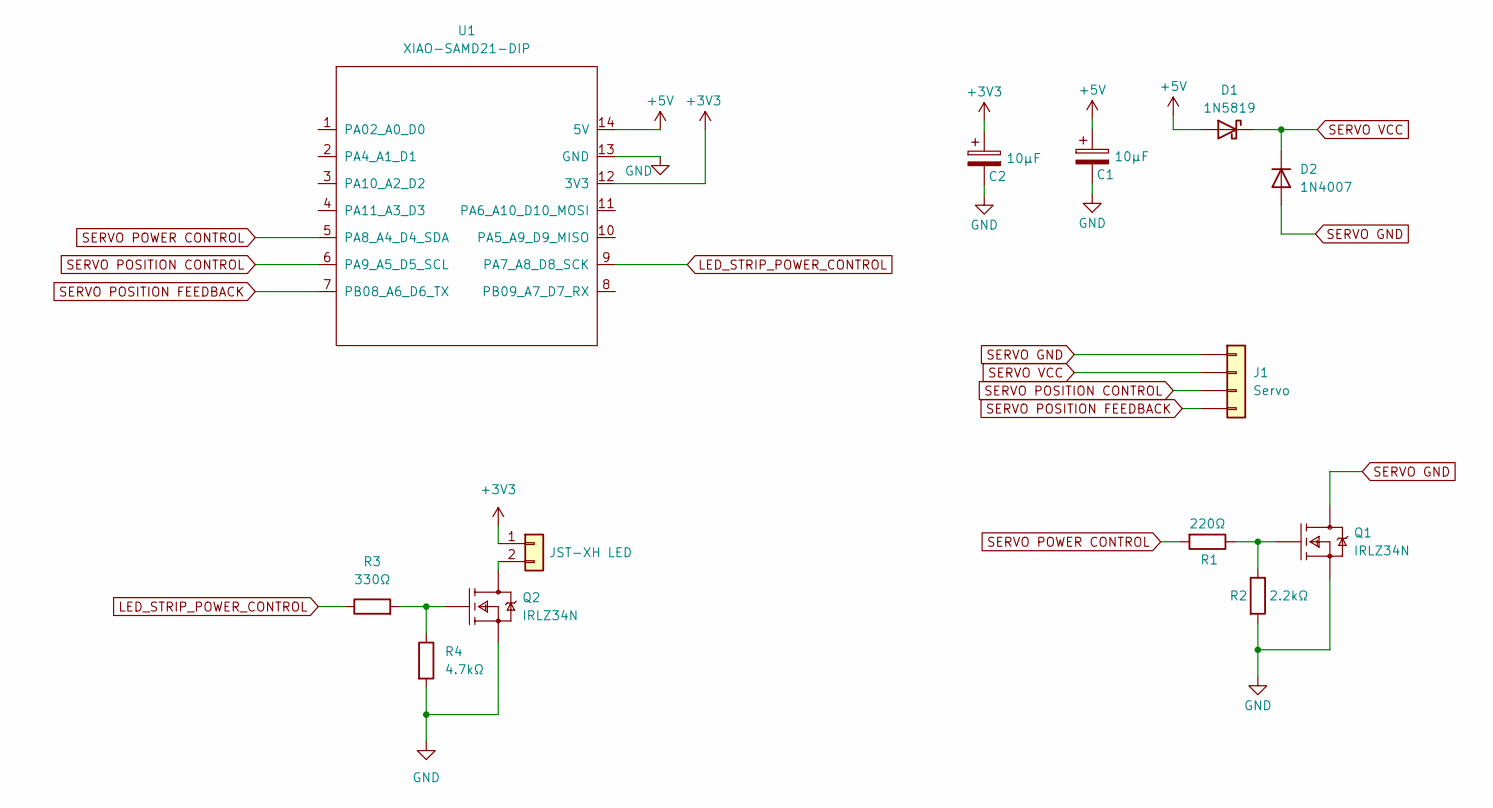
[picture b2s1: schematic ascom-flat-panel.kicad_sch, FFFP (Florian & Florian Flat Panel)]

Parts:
C1, C2: 10µF; C_Radial_D6.3mm_H11.0mm_P2.50mm
D1: 1N5819; D_DO-41_SOD81_P10.16mm_Horizontal
D2: 1N4007; D_DO-41_SOD81_P10.16mm_Horizontal
J1: Servo; PinHeader_1x04_P2.54mm_Vertical
J2: JST-XH LED; JST_XH_B2B-XH-A_1x02_P2.50mm_Vertical
Q1, Q2: IRLZ34N; TO-220-3_Vertical; breakdown voltage drain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 60 V; current rating 32 A; mouser part number 512-FQP30N06L; digikey description MOSFET N-CH 60V 32A TO-220
R1: 220Ω; R_Axial_DIN0207_L6.3mm_D2.5mm_P10.16mm_Horizontal
R2: 2.2kΩ; R_Axial_DIN0207_L6.3mm_D2.5mm_P10.16mm_Horizontal
R3: 330Ω; R_Axial_DIN0207_L6.3mm_D2.5mm_P10.16mm_Horizontal
R4: 4.7kΩ; R_Axial_DIN0207_L6.3mm_D2.5mm_P10.16mm_Horizontal
U1: XIAO-SAMD21-DIP

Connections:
+3V3: C2.1, J2.1, U1.12 (3V3)
+5V: C1.1, D1.2 (A), U1.14 (5V)
GND: C1.2, C2.2, Q1.3 (S), Q2.3 (S), R2.2, R4.2, U1.13 (GND)
LED_STRIP_POWER_CONTROL: R3.1, U1.9 (PA7_A8_D8_SCK)
unnamed: J2.2, Q2.2 (D)
unnamed: Q1.1 (G), R1.1, R2.1
unnamed: Q2.1 (G), R3.2, R4.1
SERVO GND: D2.2 (A), J1.1, Q1.2 (D)
SERVO POSITION CONTROL: J1.3, U1.6 (PA9_A5_D5_SCL)
SERVO POSITION FEEDBACK: J1.4, U1.7 (PB08_A6_D6_TX)
SERVO POWER CONTROL: R1.2, U1.5 (PA8_A4_D4_SDA)
SERVO VCC: D1.1 (K), D2.1 (K), J1.2

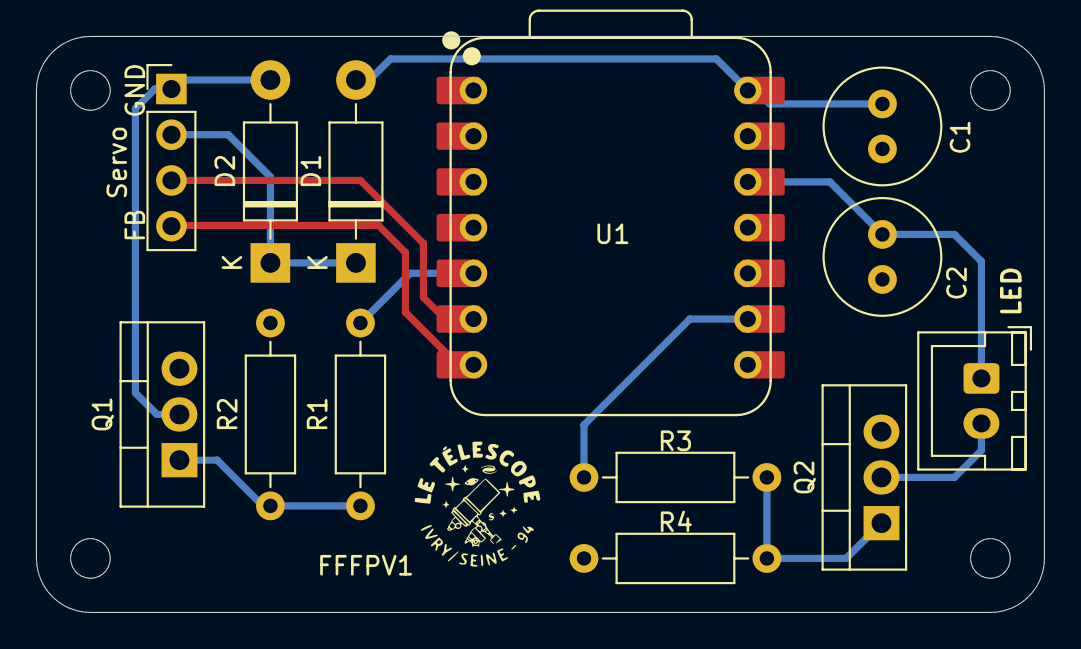
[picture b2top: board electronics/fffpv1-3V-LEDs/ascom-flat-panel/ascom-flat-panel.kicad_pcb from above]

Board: 2 copper layers, 56.0 x 32.0 mm, 13 parts (0 on the bottom side), 12 nets.

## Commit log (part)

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2025-03-24 Basic cover state implem
2025-03-25 First real full implem
2025-03-26 Firware code first complete documentation draft
2025-03-26 Typos, typos, typos ...
2025-03-26 ASCOM sdk depencies as NuGets
2025-03-26 Get valid COM ports as source for combo
2025-03-27 Proper start this time
2025-03-28 ajout des bibliothèque de symboles et empreintes Seeeduino XIAO + mise à jour du schéma avec ces éléments + draft de pcb
2025-03-28 First driver full implem
2025-03-28 Minor adjustments
2025-03-28 Fix minor conection bug
2025-03-29 Clearer error message for device validation
2025-03-29 Driver state was set before the hardware did actually try to connect
2025-03-30 Should be ok for firmware testing
2025-03-31 ajout perçage pour fixation + réajustement position logo club
2025-03-31 Proper validation
2025-03-31 ajout des tolérances pcbway + quelques optimisations de routage (supression de vias)
2025-03-31 correction suite à détection d'erreur...
2025-03-31 Correct expected result for ping (#4)
2025-04-01 Indi driver init and directories layout adjustements
2025-04-01 Untracking indi drier build dir
2025-04-01 Second layer of documentation
2025-04-02 ajout logo club en gros sur couche inférieure
2025-04-02 réajustements de routage...
2025-04-02 Fix: correct error message when panel not calibrated
2025-04-02 Fix small mistakes and typos (#6)
    * Fix: Separators validation was logically incorrect
    * Fix: correct error message when panel not calibrated
    * Fix: Typos in firmware ino file top comment
    * Fix : Typos a bit everywhere
2025-04-03 Typos typos typos everywhere
2025-04-04 Open serial connection after init
2025-04-08 [kicad] - schéma : alimentation des LEDs passée de 3V3 à 5V suite aux tests
2025-04-08 [kicad] - mise à jour valeur résistance 5k -> 4k7 suivant tests + ajustement de routage
2025-04-08 [kicad] - mise à jour screenshots
2025-04-08 Adding models entry in readme
2025-04-09 [kicad] - Modification empreinte du Condensateur par cohérence avec les composants reçus (diam 6.3 au lieu de 5)
2025-04-19 [kicad] - Modif suite aux tests servo : valeur R2 + routage connecteur
2025-04-21 [ASCOM] Revert fake cover status quick fix
2025-04-21 Ft kicad update (#11)
    * [kicad] - Modification empreinte du Condensateur par cohérence avec les composants reçus (diam 6.3 au lieu de 5)
    * [kicad] - suppression du plan de masse de la couche supérieure de cuivre, a priori inutilisé
    * [kicad] - Modif suite aux tests servo : valeur R2 + routage connecteur
    * [kicad] - optimisation placement des connecteurs
    * [kicad] - suppression des vias, ajustement des trous (M2) et arrondi des angles
    * [ASCOM] Revert fake cover status quick fix
2025-04-22 [documentation] - Broken link to protocol specs in readme
2025-04-22 [firmware] - Let's try to converge first
2025-04-23 [firware][documentation] - Minor changes and housekeeping
2025-04-23 [documentation] - Correct calibration command name
2025-04-26 [3D] adapting clamp head to servo box size
2025-04-27 [kicad] - suppression des 2 couches internes de Cu inutiles suite à reviex pcbway. Mise à jour du pcb et des fichiers gerber
2025-04-27 [3D] - First cover implem
2025-04-28 [3D] - circuit box : encapsulement dans un objet Part
2025-04-28 [3D] - circuit box : ajout d'un bracket de fixation repris de jlecomte + ajustement des tailles de visserie suivant mesure
2025-04-28 [3D] - ajout d'un fichier avec le modèle de la boite à servo adaptée de jlecomte [le nom de cette branche n'a plus aucun sens xD]
2025-04-29 [3D] - cf commit précédent, ajout du mauvais fichier
2025-05-06 [3D] - perçage pour fixation du support de boite pcb
2025-05-08 [3D] - implémentation de la possibilité de rotation du couvercle via "Transformation" (par déplacement de son origine sur l'axe) + déplacement vers le bas de la boite pcb + modification provisoire du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
2025-05-08 [3D] - repositionnement de la boite pcb suite à l'agradissement de la pince, et rétablissement des dimensions intiales de son support
2025-05-14 [firmware] - Non blocking blink
2025-05-14 [firmware] - Arduino folder naming conventions
2025-05-14 [firmaware] - Status LED is ON during calibration
2025-05-19 [3D] - Finalisation nouveau panneau (sauf fixations bras) - retour dans fichier principal
2025-05-19 [3D] - nettoyage
2025-05-21 [3D] - cavité de passage de cable dans le bras droit
2025-05-22 [3D] - cavité de passage de cables dans le corps du panneau (TODO : prolonger dans diffuseur latéral...)
2025-05-23 [3D] - initialisation bras gauche
2025-05-26 [3D] - ajustement de la position de la boite pcb + modification de son support
2025-05-26 [3D] - emplacements pour aimants pince/panneau
2025-05-26 [3D] - ajustement perçage pour fixation bras/servo
2025-05-26 [3D] - chanfrein panneau
2025-05-26 [3D] - chanfreins bras
2025-05-28 [3D] - suppression de doublons dans les paramètres
2025-05-30 [3D] - ServoBoxInserts : ajustement diamètre et profondeur trous inserts suivant inserts M2 en stock
2025-06-02 [3D] - LOGOOOOOOOOOO !!!!
2025-06-03 [3D Model] Intégration et finalisation modèle 3D proto (#17)
    * [3D] - intialisation boite pcb. TODO :
    - passe cables
    - trous pour fixation à la pince
    - support aimants
    - ajustement position USB-C (en particulier prendre en compte épaisseurs connecteurs seeduino)
    * [3D] adapting clamp head to servo box size
2025-06-06 [3D] - correction intégration logo (plus de dépassement du plan du boîtier)
2025-06-14 Add ASCOM driver installer script
2025-06-15 [driver] Enabling driver installer welcome page
2025-06-17 [Firmware] Minor tweaks
2025-06-18 [3D] - Circuit Box : inserts + aimants en surface
2025-06-18 [3D] - chanfreins sur les cavités pour aimants
2025-06-18 [3D] - corps panneau : inserts M3 pour fixation du couvercle du panneau
2025-06-18 [driver-firmware] Max brightness value is 2047 expermimentatlly. CPU clock is the limiting factor here
2025-06-19 [3D] - réajustement du diamètre intérieur du panneau : ajusté sur le diamètre du panneau de LEDs plutôt que sur le diamètre du télescope
2025-06-19 [firmware] Typos in the comments
2025-06-20 [3D] - Final touch !
2025-06-21 [circuit] LEDS on 3V Ki-Cad project init
2025-06-21 [circuit] PCB modified accordingly to schematics
2025-06-21 [circuit] cosmetics
2025-06-21 micro ajustement cosmétique
2025-06-23 [electronics] Various fixes for the 3v output led circuit (#22)
    * micro ajustement cosmétique
    * mise à jour des fichiers de fab
    * suppression des fichiers de fab 5V et 3V -> à mettre en release
    ---------
2025-06-23 [documentation] Starting to fill blanks
2025-06-28 [documentation] Install and uploads
2025-06-29 [documentation] minor fixes
2025-06-29 [documentation] link is an image in fact
2025-06-30 Badges update
2025-06-30 [docummentation] testing latest release
2025-06-30 [documentation] license badge
2025-06-30 [documentation] update license badge
2025-06-30 [documentation] Initia NINA usage documentation
2025-07-01 [documentation] Thanks Fabrice
2025-07-02 [documentation] - paragraphe fabrication PCB
2025-07-05 [firmware][driver] Handle proper disconnection
2025-07-29 [3D] - réduction (-0,5 mm) de l'épaisseur du spacer/diffuseur
2025-07-30 [3D] - agrandissement trous vis/écrou M4
2025-07-31 [3D] - passe d'assainissement de la géométrie
2025-10-19 [3D] - agrandissement trou passage cable Servo Box
2025-12-28 Plateform io project init
2025-12-28 Warings but the otehr way around
2025-12-29 Formatting cpp source files
2025-12-29 Code block fences
2025-12-29 License headers
2025-12-29 Why a double dot in the generated name ?
2025-12-29 Documenting what's coming with v2
2025-12-29 Correct build output
2025-12-29 Assembly version and missing spaces
2025-12-30 Match plateformio monitor speed with FFFP speed
2025-12-30 Other typos
2026-01-01 [electronics] - initialisation schéma v2 avec panneau EL
2026-01-01 [electronics] - ajout empreintes pour C2 (A CONFIRMER) et TLC272 (AOp)
2026-01-01 First PCB routing
2026-01-02 Adding power planes to simplify PCB layout
2026-01-02 Avoiding sharp edgdes causing charge buildups
2026-01-02 Routing 2 pin connector
2026-01-02 Flip connector for shorter traces and rearanged schematics
2026-01-04 Removed most warnings form ERC (schema) and DRC (pcb)
2026-01-18 [Driver] Fetch and store firware data in setup
2026-01-18 [Driver] Displaying firmware version in Driver info
2026-02-01 Better handling of check connection in driver config
2026-02-02 Better accessibility for readme
2026-02-02 Better html practices
2026-02-07 Updatong shcematics and PCB to use DAC for EL driver PWR ctrl
2026-02-09 Misinterprete radius for diameter...
2026-02-09 Fiddling with rules
2026-02-12 Added DRC exclusion
2026-02-25 refacto à partir de master sketch + creation pince + retournement boite servo + bras bidon pour tests + creation assembly pour tester les déplacements
2026-03-01 préparation jonction bras/panneau (WIP)
2026-03-04 perçage de cables bras/panneau
2026-03-04 petite révision de l'affinage de la pince
2026-03-05 rotation d'1/6e de tour des trous hexagonaux de la boite servo pour s'adapter au sens d'impression
2026-03-05 perçage trous de fixation pince/boite circuit
2026-03-06 congés trou RCA et usb
2026-03-06 chanfreins externes boite circuit
2026-03-09 perçage de jonction bras/servo
2026-03-15 Ajout d'une tranchée en double spirale paramétrable par la spreadsheet pour le chauffage du panneau. Elle est générée par la macro jointe au projet. L'autre macro sert à la supprimer (il est sans dou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
2026-03-19 REX CBox : augmentation taille trous M2
2026-03-19 correction erreur sur pince à cause des modifs de trous CBox
2026-03-20 REX CBOX v2 : correction encoche pour tete de vis M3
2026-03-27 première passe de réparations (références manquantes)
2026-03-27 chanfreins pour trous inserts panneau
2026-03-27 ajustement des profondeurs de trous
2026-04-01 Let's make it recompile
2026-04-01 First almost complete implem
2026-04-02 Should be close to the real deal now
2026-04-02 Correct version
2026-04-03 Reordering stuff for update to take account brightness values
2026-04-03 Should report brightness value now
2026-04-03 Update on cap status
2026-04-03 Fix: Let's try to get coherent light statuses
2026-04-05 suite travaux mise à l'échelle panneau 110 mm
2026-04-06 Fix requests
2026-04-06 Updating readme
2026-04-07 quelques réparations sur modèle 110mm
2026-04-10 création modèle générique pour tests scalabilité
2026-04-16 160mm : texte libre sur boite servo
2026-04-29 mise à l'échelle : réduction du nombre de paramètres à modifier
2026-05-01 mise à l'echelle : paramétrage distance boite servo - bras gauche
2026-05-01 mise à l'échelle : correction passage cable bras/panneau
2026-05-05 ajustement macro spirale pour caler disque central sur un pitch
2026-05-21 ajout repertoire local de polices et macro pour relocaliser les paths des Shapestring en cas de changement de PC (oui, c'est triste d'avoir à faire ça)
2026-05-30 ajout d'un jeu (0.2 mm) entre le bushing et le bras (modèle 160 uniquement pour l'instant)
2026-06-26 We are dumb but we know how to patch things quicly. When servo spins in other direction, you'd better deal with it...
2026-06-27 Updating specs wiht new v2 commands
